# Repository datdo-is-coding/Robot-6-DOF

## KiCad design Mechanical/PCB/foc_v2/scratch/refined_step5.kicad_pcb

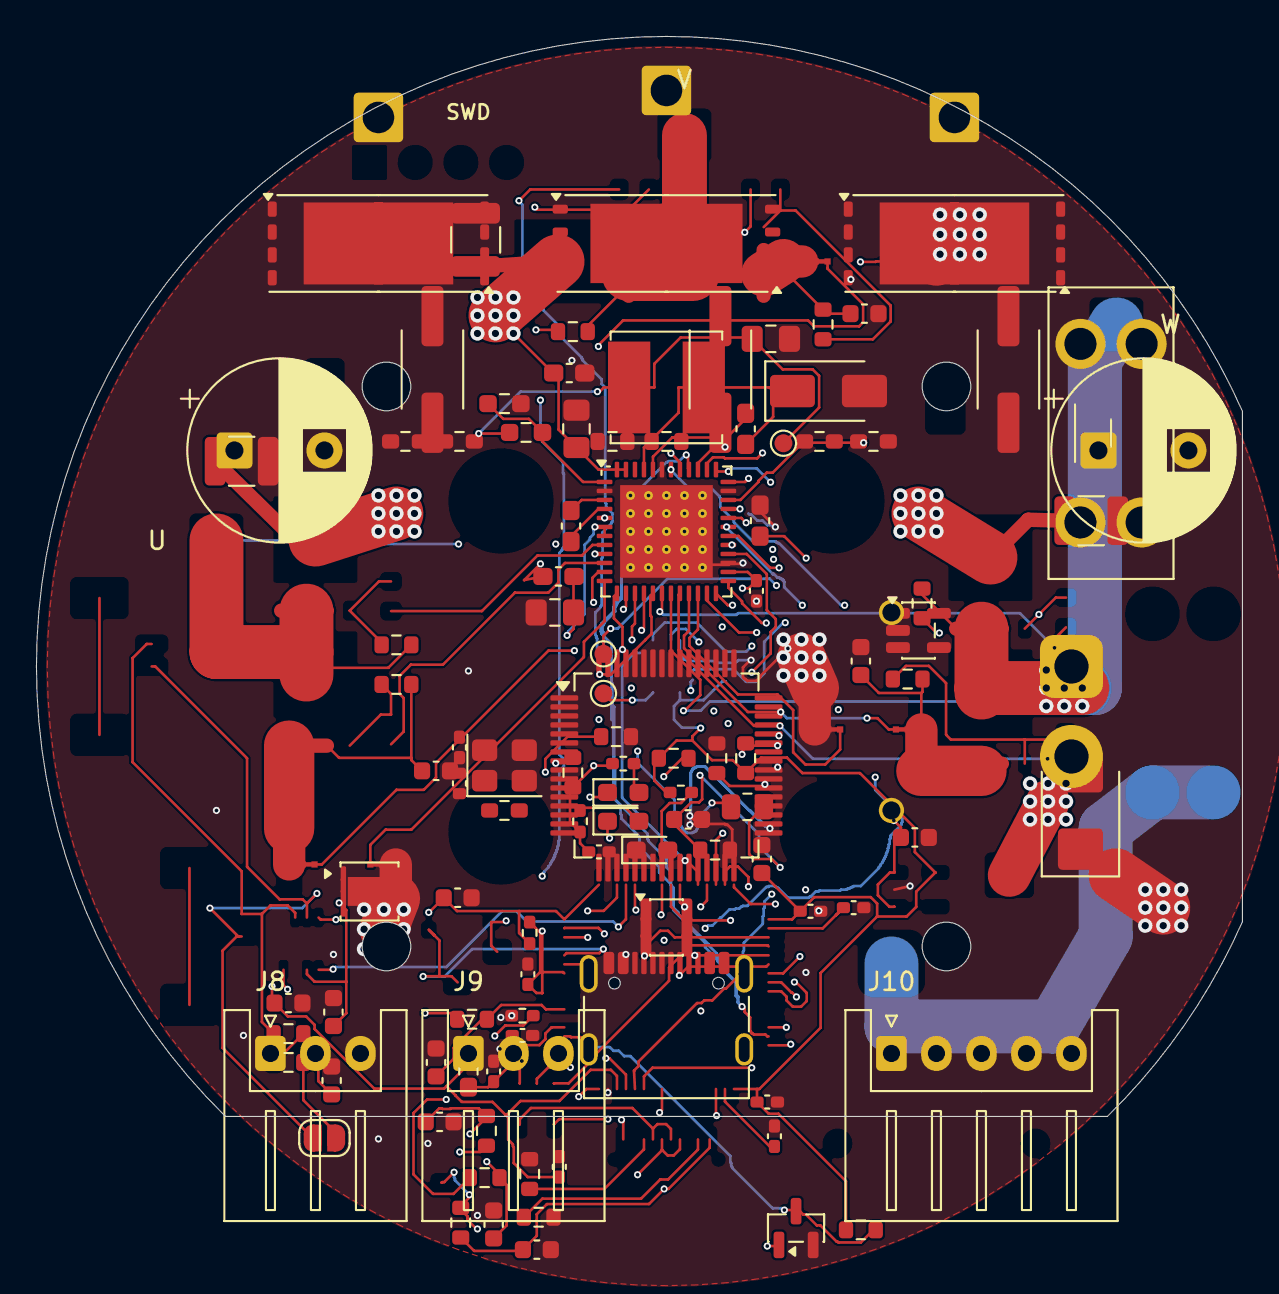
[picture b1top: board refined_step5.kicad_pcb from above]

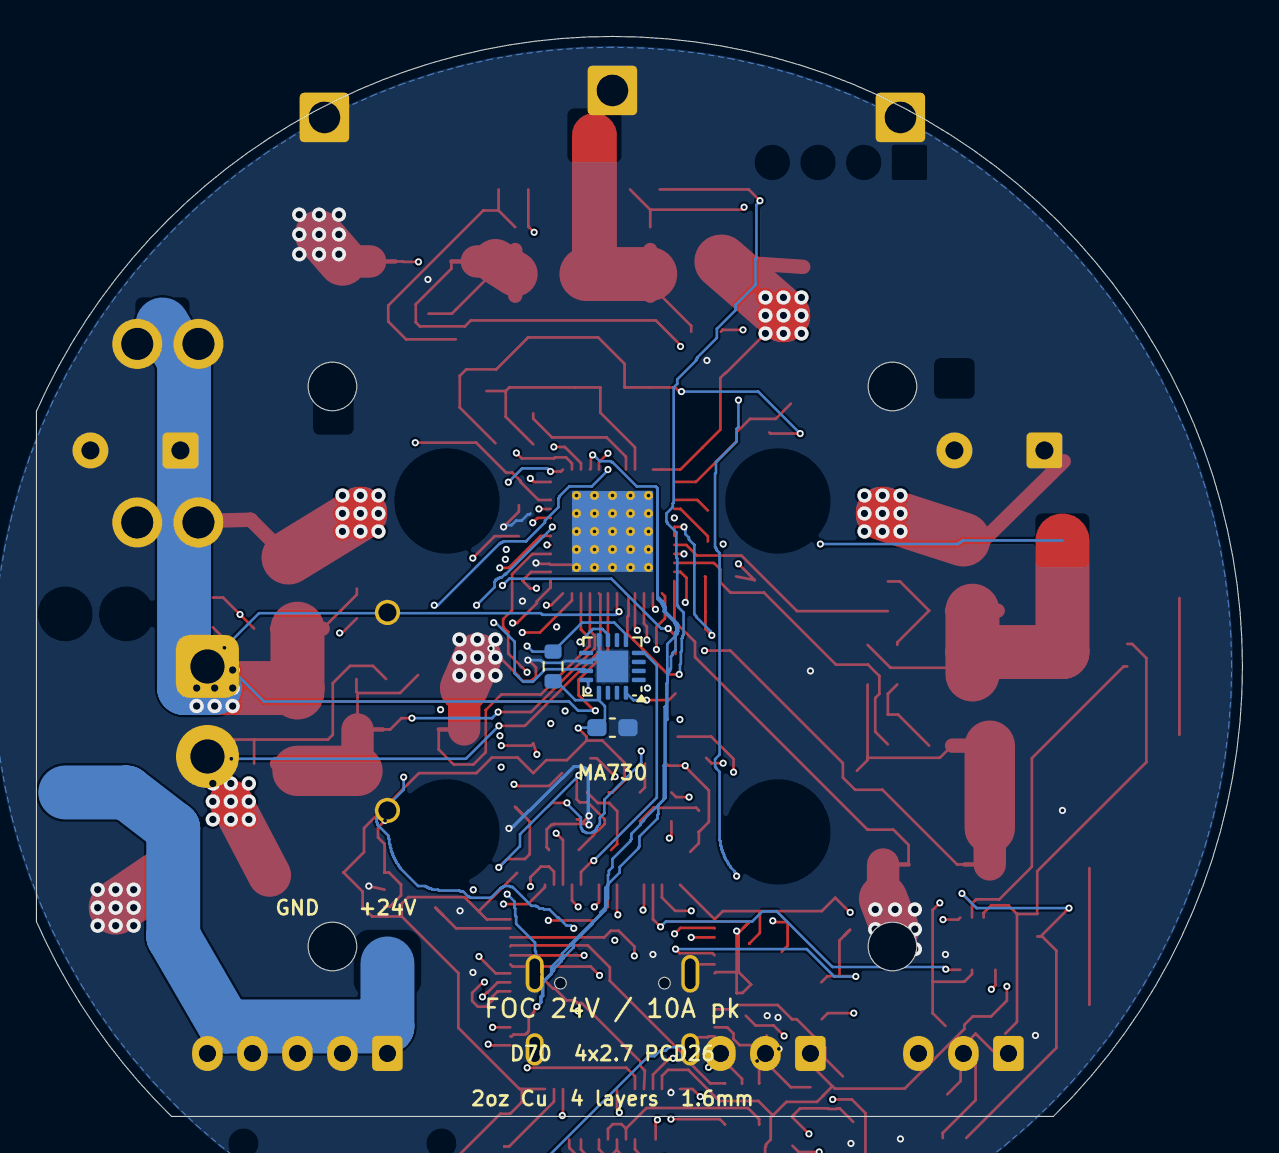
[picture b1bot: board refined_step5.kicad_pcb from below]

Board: 4 copper layers, 67.0 x 60.0 mm, 124 parts (3 on the bottom side), 91 nets.

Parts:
C1, C2, C3, C54, C55, C56: 1nF; C_0603_1608Metric
C4, C5, C7, C21, C50, C51, C52: 100nF; C_0402_1005Metric_Pad0.74x0.62mm_HandSolder
C6: 1uF; C_0402_1005Metric_Pad0.74x0.62mm_HandSolder
C8, C9: 33pF; C_0402_1005Metric_Pad0.74x0.62mm_HandSolder
C10, C11: 2.2uF; C_0402_1005Metric_Pad0.74x0.62mm_HandSolder
C12, C17: 10uF; C_0805_2012Metric_Pad1.18x1.45mm_HandSolder
C13, C15: 0.1uF; C_0603_1608Metric_Pad1.08x0.95mm_HandSolder
C14, C18, C20: 1uF; C_0603_1608Metric_Pad1.08x0.95mm_HandSolder
C16: 22uF; C_0805_2012Metric_Pad1.18x1.45mm_HandSolder
C19: 47nF; C_0603_1608Metric_Pad1.08x0.95mm_HandSolder
C53, C59, C60, C61: 100nF; C_0603_1608Metric
C57: 1uF; C_0603_1608Metric
C58: 4.7uF; C_0603_1608Metric
C62: 4.7nF; C_0603_1608Metric
C63: 470uF; CP_Radial_D10.0mm_P5.00mm
C64: 10nF; C_0603_1608Metric
C_BULK1: 470uF; CP_Radial_D10.0mm_P5.00mm
C_BUS1, C_BUS2, C_BUS3: 10uF; C_1210_3225Metric
D1, D2: LED RED; LED_0603_1608Metric_Pad1.05x0.95mm_HandSolder
D3: LED GREEN; LED_0603_1608Metric_Pad1.05x0.95mm_HandSolder
D4: SS16; D_SMA
D6: SMBJ30A; D_SMB
F1: 10A 58V; Fuseholder_Blade_Mini_Keystone_3568
FB1: 600R@100MHz; L_0603_1608Metric_Pad1.05x0.95mm_HandSolder
H1, H2, H3, H4: M2.5 PCD26; MountingHole_2.7mm_M2.5
IC1: DRV8323RSRGZR; Texas_RGZ0048A_VQFN-48-1EP_7x7mm_P0.5mm_EP5.15x5.15mm_Therm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
J1: PHASE_U; SolderWire-1sqmm_1x01_D1.4mm_OD2.7mm
J2: PHASE_V; SolderWire-1sqmm_1x01_D1.4mm_OD2.7mm
J3: PHASE_W; SolderWire-1sqmm_1x01_D1.4mm_OD2.7mm
J7: USB_C_Receptacle_USB2.0_16P; USB_C_Receptacle_G-Switch_GT-USB-7010ASV
J8, J9: Conn_01x03; JST_XH_S3B-XH-A_1x03_P2.50mm_Horizontal
J10: SWD; JST_XH_S5B-XH-A_1x05_P2.50mm_Horizontal
J11: 24V_IN; AMASS_XT30PW-M_Edge_NoSilk
JP1: TERM_ENABLE; SolderJumper-2_P1.3mm_Open_RoundedPad1.0x1.5mm
L1: 22uH; L_Bourns_SRN6045TA
NT1: KELVIN_CSA_SPA; NetTie_Kelvin
NT2: KELVIN_SNA; NetTie_Kelvin
NT3: KELVIN_CSA_SPB; NetTie_Kelvin
NT4: KELVIN_SNB; NetTie_Kelvin
NT5: KELVIN_CSA_SPC; NetTie_Kelvin
NT6: KELVIN_SNC; NetTie_Kelvin
Q1, Q2, Q3, Q4, Q5, Q6: CSD18532Q5B; TDSON-8-1
Q7: 2N7002; SOT-23
R1, R2, R3, R4, R5, R7: 2.2R; R_0603_1608Metric
R6: 18k; R_0603_1608Metric_Pad0.98x0.95mm_HandSolder
R8, R42, R43, R52, R54, R61: 10k; R_0603_1608Metric
R9: 3k3; R_0603_1608Metric_Pad0.98x0.95mm_HandSolder
R10, R50, R55, R56, R57, R58, R59, R60: 100k; R_0603_1608Metric
R32, R34: 10k; R_0402_1005Metric_Pad0.72x0.64mm_HandSolder
R33, R35, R36: 1k; R_0402_1005Metric_Pad0.72x0.64mm_HandSolder
R37, R38, R39: 100R; R_0603_1608Metric
R40, R41: 5.1k; R_0603_1608Metric
R44: 1M; R_0603_1608Metric
R45, R46: 60.4R; R_0603_1608Metric
R47, R48, R49: 5m; R_2512_6332Metric
R51: 4.7k; R_0603_1608Metric
R53: 150k; R_0805_2012Metric
TP1: TestPoint; TestPoint_Pad_D1.0mm
TP2: MGH_TP; TestPoint_Pad_D1.0mm
TP3: MGL_TP; TestPoint_Pad_D1.0mm
U1: STM32F405RGTx; LQFP-64_10x10mm_P0.5mm
U2: MA730; MA730_QFN16_3x3
U8: USBLC6-2SC6; SOT-23-6
U9: TJA1051TK-3; HVSON-8-1EP_3x3mm_P0.65mm_EP1.6x2.4mm
U10: AP2112K-3.3; SOT-23-5
Y1: 12MHz; Crystal_SMD_3225-4Pin_3.2x2.5mm

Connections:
+3V3: C4.1, C14.2, C21.2, C50.1, C51.1, C52.1, C53.1, C58.1, C60.1, FB1.2, IC1.26 (VREF), J10.1, R8.1, R32.1, R33.1, R35.1, R36.1, R42.1, R51.1, R52.1, R61.1, U1.1 (VBAT), U1.19 (VDD), U1.32 (VDD), U1.48 (VDD), U1.64 (VDD), U2.13 (VDD), U9.5 (VIO), U10.5 (VOUT)
+3V3A: C5.1, C6.1, FB1.1, U1.13 (VDDA)
+5V: C16.1, C57.1, C61.1, L1.1, R6.1, TP1.1 (1_1), U9.3 (VCC), U10.1 (VIN), U10.3 (EN)
/COMMUNICATION/CAN_H: J8.1, J9.1, R45.1, U9.7 (CANH)
/COMMUNICATION/CAN_L: J8.2, J9.2, JP1.1 (A), U9.6 (CANL)
/COMMUNICATION/CAN_RX: U1.61 (PB8), U9.4 (RXD)
/COMMUNICATION/CAN_TX: U1.62 (PB9), U9.1 (TXD)
/COMMUNICATION/CC1: J7.A5 (CC1), R40.1
/COMMUNICATION/CC2: J7.B5 (CC2), R41.1
/COMMUNICATION/USB_DM_CONN: J7.A7 (D-), J7.B7 (D-), U8.1 (I/O1)
/COMMUNICATION/USB_DP_CONN: J7.A6 (D+), J7.B6 (D+), U8.3 (I/O2)
/COMMUNICATION/USB_N: U1.44 (PA11), U8.6 (I/O1)
/COMMUNICATION/USB_P: U1.45 (PA12), U8.4 (I/O2)
/COMMUNICATION/USB_VBUS: Q7.3 (D), R42.2, U1.14 (PA0)
/COMMUNICATION/VBUS: C59.1, J7.A4 (VBUS), J7.A9 (VBUS), J7.B4 (VBUS), J7.B9 (VBUS), R43.1, U8.5 (VBUS)
/COMMUNICATION/VBUS_GATE: Q7.1 (G), R43.2, R44.1
/GATE_DRV/CSA_CAL1: IC1.34 (CAL), R50.1, U1.24 (PC4)
/GATE_DRV/CSA_SPA: IC1.11 (SPA), NT1.1
/GATE_DRV/CSA_SPB: IC1.14 (SPB), NT3.1
/GATE_DRV/CSA_SPC: IC1.21 (SPC), NT5.1
/GATE_DRV/EN_GATE1: IC1.33 (ENABLE), R10.1, U1.40 (PC9)
/GATE_DRV/GHA: IC1.8 (GHA), R1.1
/GATE_DRV/GHB: IC1.17 (GHB), R3.1
/GATE_DRV/GHC: IC1.18 (GHC), R5.1
/GATE_DRV/GLA: IC1.10 (GLA), R2.1
/GATE_DRV/GLB: IC1.15 (GLB), R4.1
/GATE_DRV/GLC: IC1.20 (GLC), R7.1
/GATE_DRV/ISENSE1_A: IC1.25 (SOA), R37.1
/GATE_DRV/ISENSE1_B: IC1.24 (SOB), R38.1
/GATE_DRV/ISENSE1_C: IC1.23 (SOC), R39.1
/GATE_DRV/NFAULT1: IC1.28 (NFAULT), R8.2, U1.30 (PB11)
/GATE_DRV/PV_SENSE: C64.1, R53.2, R54.1, U1.22 (PA6)
/GATE_DRV/PWM1_A: IC1.37 (INHA), U1.41 (PA8)
/GATE_DRV/PWM1_AN: IC1.38 (INLA), U1.34 (PB13)
/GATE_DRV/PWM1_B: IC1.39 (INHB), U1.42 (PA9)
/GATE_DRV/PWM1_BN: IC1.40 (INLB), U1.35 (PB14)
/GATE_DRV/PWM1_C: IC1.41 (INHC), U1.43 (PA10)
/GATE_DRV/PWM1_CN: IC1.42 (INLC), U1.36 (PB15)
/GATE_DRV/SHA: IC1.9 (SHA), J1.1 (1_1), Q1.1 (S), Q1.2 (S), Q1.3 (S), Q2.5 (D), R55.2
/GATE_DRV/SHB: IC1.16 (SHB), J2.1 (1_1), Q3.1 (S), Q3.2 (S), Q3.3 (S), Q4.5 (D), R57.2
/GATE_DRV/SHC: IC1.19 (SHC), J3.1 (1_1), Q5.1 (S), Q5.2 (S), Q5.3 (S), Q6.5 (D), R59.2
/GATE_DRV/SNA: IC1.12 (SNA), NT2.1
/GATE_DRV/SNB: IC1.13 (SNB), NT4.1
/GATE_DRV/SNC: IC1.22 (SNC), NT6.1
/GATE_DRV/SPA: C1.1, NT1.2, Q2.1 (S), Q2.2 (S), Q2.3 (S), R47.1, R56.2
/GATE_DRV/SPB: C2.1, NT3.2, Q4.1 (S), Q4.2 (S), Q4.3 (S), R48.1, R58.2
/GATE_DRV/SPC: C3.1, NT5.2, Q6.1 (S), Q6.2 (S), Q6.3 (S), R49.1, R60.2
/GATE_DRV/SPI1_MISO: IC1.29 (SDO), R51.2, U1.56 (PB4)
/GATE_DRV/SPI1_MOSI: IC1.30 (SDI), U1.57 (PB5)
/GATE_DRV/SPI1_SCK: IC1.31 (SCLK), U1.21 (PA5)
/GATE_DRV/SPI1_SS0: IC1.32 (NSCS), R52.2, U1.51 (PC10)
/HALL/HALL_CS: R61.2, U1.50 (PA15), U2.5 (~CS)
/HALL/HALL_MISO: U1.52 (PC11), U2.7 (MISO)
/HALL/HALL_MOSI: U1.53 (PC12), U2.4 (MOSI)
/HALL/HALL_SCLK: U1.55 (PB3), U2.12 (SCLK)
/MCU/ADC_IA: C54.1, R37.2, U1.11 (PC3)
/MCU/ADC_IB: C55.1, R38.2, U1.17 (PA3)
/MCU/ADC_IC: C56.1, R39.2, U1.20 (PA4)
/MCU/BOOT0: R34.2, U1.60 (BOOT0)
/MCU/LED_G: D3.1 (K), U1.3 (PC14)
/MCU/LED_R: D2.1 (K), U1.2 (PC13)
/MCU/NRST: C7.1, J10.4, R32.2, U1.7 (NRST)
/MCU/OSC_IN: C8.2, U1.5 (PH0), Y1.1
/MCU/OSC_OUT: C9.2, U1.6 (PH1), Y1.3
/MCU/SWCLK: J10.3, U1.49 (PA14)
/MCU/SWDIO: J10.2, U1.46 (PA13)
DVDD: C20.1, IC1.36 (DVDD)
GND: C1.2, C2.2, C3.2, C4.2, C5.2, C6.2, C7.2, C8.1, C9.1, C10.2, C11.2, C12.2, C13.2, C14.1, C16.2, C17.1, C20.2, C21.1, C50.2, C51.2, C52.2, C53.2, C54.2, C55.2, C56.2, C57.2, C58.2, C59.2, C60.2, C61.2, C62.2, C63.2, C64.2, C_BULK1.2, C_BUS1.2, C_BUS2.2, C_BUS3.2, D1.1 (K), D4.2 (A), D6.2 (A), IC1.2 (PGND), IC1.27 (DGND), IC1.35 (AGND), IC1.43 (BGND), IC1.49 (THERMAL_PAD), J7.A1 (GND), J7.A12 (GND), J7.B1 (GND), J7.B12 (GND), J7.SH (SHIELD), J8.3, J9.3, J10.5, J11.2, NT2.2, NT4.2, NT6.2, Q7.2 (S), R9.2, R10.2, R34.1, R40.2, R41.2, R44.2, R47.2, R48.2, R49.2, R50.2, R54.2, U1.12 (VSSA), U1.18 (VSS), U1.63 (VSS), U2.8 (GND), U2.10 (TEST), U2.17 (PAD), U8.2 (GND), U9.2 (GND), U9.8 (S), U9.9 (GND), U10.2 (GND), Y1.2 (G), Y1.4 (G)
unnamed: C62.1, R45.2, R46.1
unnamed: D1.2 (A), R33.2
unnamed: D2.2 (A), R35.2
unnamed: D3.2 (A), R36.2
unnamed: C15.1, D4.1 (K), IC1.45 (SW), L1.2
unnamed: C15.2, IC1.44 (CB)
unnamed: C19.1, IC1.4 (CPH)
unnamed: C19.2, IC1.3 (CPL)
unnamed: IC1.1 (FB), R6.2, R9.1
unnamed: C18.1, IC1.5 (VCP)
unnamed: F1.1, J11.1
unnamed: JP1.2 (B), R46.2
unnamed: Q1.4 (G), R1.2, R55.1
unnamed: Q2.4 (G), R2.2, R56.1
unnamed: Q3.4 (G), R3.2, R57.1
unnamed: Q4.4 (G), R4.2, R58.1
unnamed: Q5.4 (G), R5.2, R59.1
unnamed: Q6.4 (G), R7.2, R60.1
unnamed: C10.1, U1.31 (VCAP_1)
unnamed: C11.1, U1.47 (VCAP_2)
unnamed: TP2.1 (1_1), U2.16 (MGH)
unnamed: TP3.1 (1_1), U2.11 (MGL)
VS: C12.1, C13.1, C17.2, C18.2, C63.1, C_BULK1.1, C_BUS1.1, C_BUS2.1, C_BUS3.1, D6.1 (K), F1.2, IC1.6 (VM), IC1.7 (VDRAIN), IC1.47 (VIN), IC1.48 (NSHDN), Q1.5 (D), Q3.5 (D), Q5.5 (D), R53.1

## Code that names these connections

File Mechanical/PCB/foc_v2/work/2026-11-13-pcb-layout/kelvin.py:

"""Give the six shunt sense traces their own nets and copper pickup points."""
import runpy, copy, json, hashlib
from pathlib import Path
W=Path(__file__).resolve().parent;ROOT=W.parent.parent;OUT=W/'candidate'
g=runpy.run_path(str(W.parent/'2026-11-13-full-schematic-fix/fix_all.py'))
sx=g['sx'];S=g['S'];ch=g['children'];one=g['one'];pos=g['pos'];props=g['props'];prop=g['prop']
g['A']['gatedrv.kicad_sch']=sx.loads((ROOT/'gatedrv.kicad_sch').read_text())
# Class methods retain the module namespace returned by runpy.
g['Sheet'].save.__globals__['OUT']=OUT
m=g['Sheet']('gatedrv.kicad_sch');drv=m.sym('IC1');pins=m.pins(drv)
prop(m.sym('J11'),'Footprint','foc_v2:AMASS_XT30PW-M_Edge_NoSilk')
for pin,name in [('12','SNA'),('13','SNB'),('22','SNC')]:
 start=pins[pin]
 wire=next(n for n in ch(m.r,'wire') if start in [tuple(q[1:3]) for q in one(n,'pts')[1:]])
 ps=[tuple(q[1:3]) for q in one(wire,'pts')[1:]];end=next(q for q in ps if q!=start)
 ground=next(n for n in m.symbols() if props(n).get('Value')=='GND' and pos(n)==end)
 m.remove(ground);m.label(name,end,90 if pin in ['13','22'] else 0)
for n in ch(m.r,'label'):
 if n[1] in ['SPA','SPB','SPC'] and pos(n)[0]<185:n[1]='CSA_'+n[1]
for i,(a,b) in enumerate([('CSA_SPA','SPA'),('SNA','GND'),('CSA_SPB','SPB'),('SNB','GND'),('CSA_SPC','SPC'),('SNC','GND')],1):
 x=round(45.72+45.72*(i-1),4)
 n=m.add('Device:NetTie_2','NT'+str(i),'KELVIN_'+a,(x,254),fp='foc_v2:NetTie_Kelvin')
 one(n,'in_bom')[1]=S('no');m.tie(n,'1',a,(-5.08,0));m.tie(n,'2',b,(5.08,0),b=='GND')
m.note('Kelvin copper pickups at the inner shunt pads: NT1-NT6 are copper only, no assembled parts.',(30.48,243.84))
m.save()
lib=OUT/'foc_v2.pretty';lib.mkdir(exist_ok=True)
(lib/'NetTie_Kelvin.kicad_mod').write_text('''(footprint "NetTie_Kelvin" (version 20260206) (generator "pcbnew")
 (layer "F.Cu") (descr "Copper-only Kelvin pickup; pad 2 sits at the inner edge of a shunt power pad")
 (attr smd exclude_from_pos_files exclude_from_bom allow_missing_courtyard)
 (property "Reference" "NT" (at 0 -1) (layer "F.Fab") (effects (font (size 1 1) (thickness 0.15))))
 (property "Value" "NetTie_Kelvin" (at 0 1) (layer "F.Fab") hide (effects (font (size 1 1) (thickness 0.15))))
 (net_tie_pad_groups "1,2")
 (fp_line (start 0 0) (end 0.65 0) (stroke (width 0.25) (type solid)) (layer "F.Cu"))
 (pad "1" smd rect (at 0 0) (size 0.35 0.35) (layers "F.Cu"))
 (pad "2" smd rect (at 0.65 0) (size 0.35 0.35) (layers "F.Cu"))
)\n''')
(OUT/'fp-lib-table').write_text('(fp_lib_table (version 7) (lib (name "foc_v2") (type "KiCad") (uri "${KIPRJMOD}/foc_v2.pretty") (options "") (descr "Copper Kelvin pickups")))\n')
print('Six copper-only Kelvin pickups added; MCU pin allocation unchanged.')
